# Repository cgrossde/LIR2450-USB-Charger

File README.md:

# LIR2450 USB Charger

**Warning:** The board arrived and the circuit does charge coin cells but the led indicator for a full charge does not work. Currently I don't know why. Any hints are appreciated.

I started doing a lot with low power devices (Arduino, BLE 4.0) and coin cells are a convenient power source. Lately I found out that there are even rechargeable coin cells. That's why I needed a charger. There are only a few models out there which are either expensive or have a charge current that I think is to high. So I made my own.

[3D-Model on Sketchfab](https://sketchfab.com/models/f6b9f5c950564a3f85bb46c3d435a189)

It is based on the [MCP73831](https://www.sparkfun.com/datasheets/Prototyping/Batteries/MCP73831T.pdf). 
Order three PCBs for 13.60$ at OSHPARK: [LIR2450 USB Charger](https://oshpark.com/projects/roORU8h6)

There are two charge modes:
 
- fast (45mA)
- slow (25mA)

Max charge current for a coin cell is usually between 80% and two third of it's capacity. So you could charge a 100mA coin cell with 80mA. I wanted to increase the lifetime of my coin cells and reduced the charge current. If you want to have different currents here is the equation to calculate R_SLOW/R_FAST:

`mA = 1000 / R in kΩ`

Example: 1000/20kΩ = 50mA

## PCB height vs USB port

The PCB is usually only 1.6mm thick which means another 0.8mm are needed so that this PCB fits nicely into a USB port without falling out. That means you need to tin the USB connector which might gain you another 0.4mm and then add some ducktape or paper to the backside until the USB connector is around 2.4mm in height.

## BOM

- MCP73831 SOT-23-5
- 0603 LED Green (~3.1V voltage drop)
- 0603 LED Orange (~2V voltage drop)
- 0805 Resistor 200Ω
- 0805 Resistor 320Ω
- 0805 Resistor 40kΩ
- 0805 Resistor 22kΩ
- 2x 0805 Capacitor 4.7uF
- CR/LIR2450 Coin cell holder (20mm diameter, 5mm height)
- (optional) male pin header, jst pin header

## Schematics

Checkout `PCB-Masks` folder if you want to etch it on your own.

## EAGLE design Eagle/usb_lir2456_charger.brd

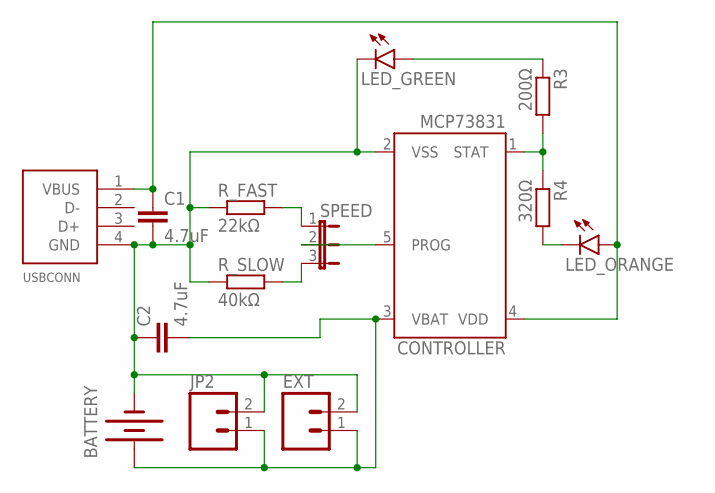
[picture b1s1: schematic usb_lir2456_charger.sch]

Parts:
BATTERY: BATTERY20PTH; BATTCOM_20MM_PTH
C1, C2: 4.7uF; C0805
CONTROLLER: MCP73831; SOT23-5
EXT: M02PTH; 1X02
JP2: M02JST-PTH-VERT; JST-2-PTH-VERT
LED_GREEN: LED0603; LED-0603
LED_ORANGE: LED0603; LED-0603
R3: 200Ω; R0805
R4: 320Ω; R0805
R_FAST: 22kΩ; R0805
R_SLOW: 40kΩ; R0805
SPEED: JP2E; JP2
USBCONN: USB-CON-4PIN; USB-MALE-A-PCB

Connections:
GND: BATTERY.2 (-), C1.2, C2.1, CONTROLLER.2 (VSS), EXT.2, JP2.2, LED_GREEN.C, R_FAST.1, R_SLOW.1, USBCONN.4 (GND)
unnamed: CONTROLLER.1 (STAT), R3.2, R4.1
unnamed: CONTROLLER.5 (PROG), SPEED.2
unnamed: LED_GREEN.A, R3.1
unnamed: R_SLOW.2, SPEED.3
unnamed: R_FAST.2, SPEED.1
unnamed: LED_ORANGE.C, R4.2
unnamed: BATTERY.1 (+), C2.2, CONTROLLER.3 (VBAT), EXT.1, JP2.1
VCC: C1.1, CONTROLLER.4 (VDD), LED_ORANGE.A, USBCONN.1 (VBUS)

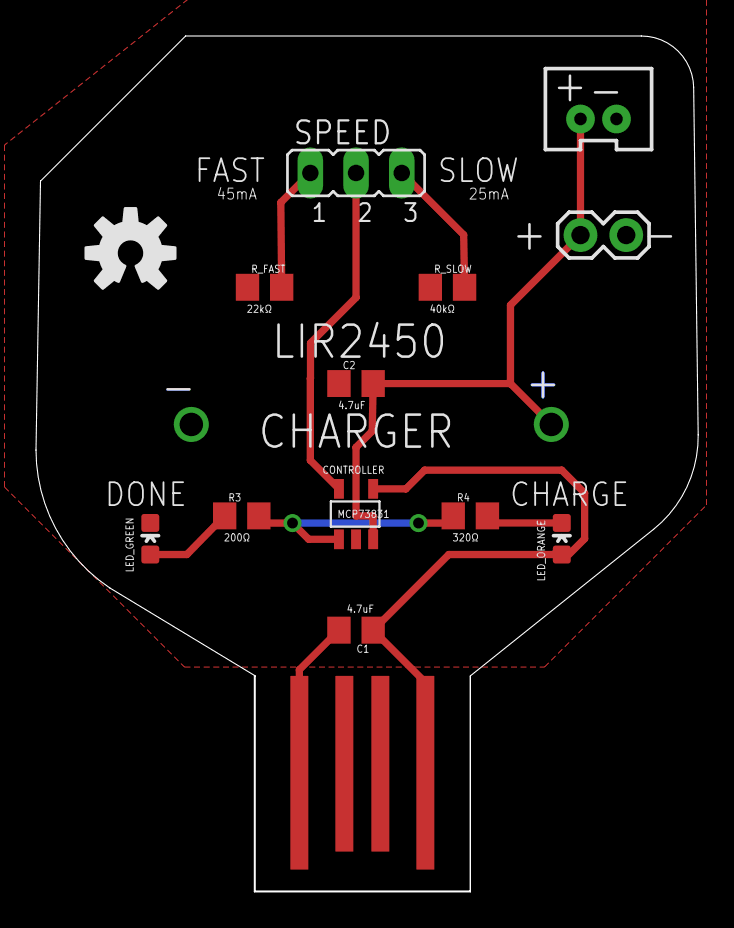
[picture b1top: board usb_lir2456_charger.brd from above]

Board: 2 copper layers, 36.8 x 47.5 mm, 15 parts (1 on the bottom side), 9 nets.

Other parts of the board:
U$1: OSHW-LOGO-M

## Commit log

2015-02-10 Fixed BOM
2015-02-10 Added link to Sketchfab model
2015-02-11 Updated 3D-Model
2015-02-11 Cropped 3D-model images

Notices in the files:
parts and their libraries:
GeekAmmo: Licensing:Creative Commons ShareAlike 4.0 International - https://creativecommons.org/licenses/by-sa/4.0
